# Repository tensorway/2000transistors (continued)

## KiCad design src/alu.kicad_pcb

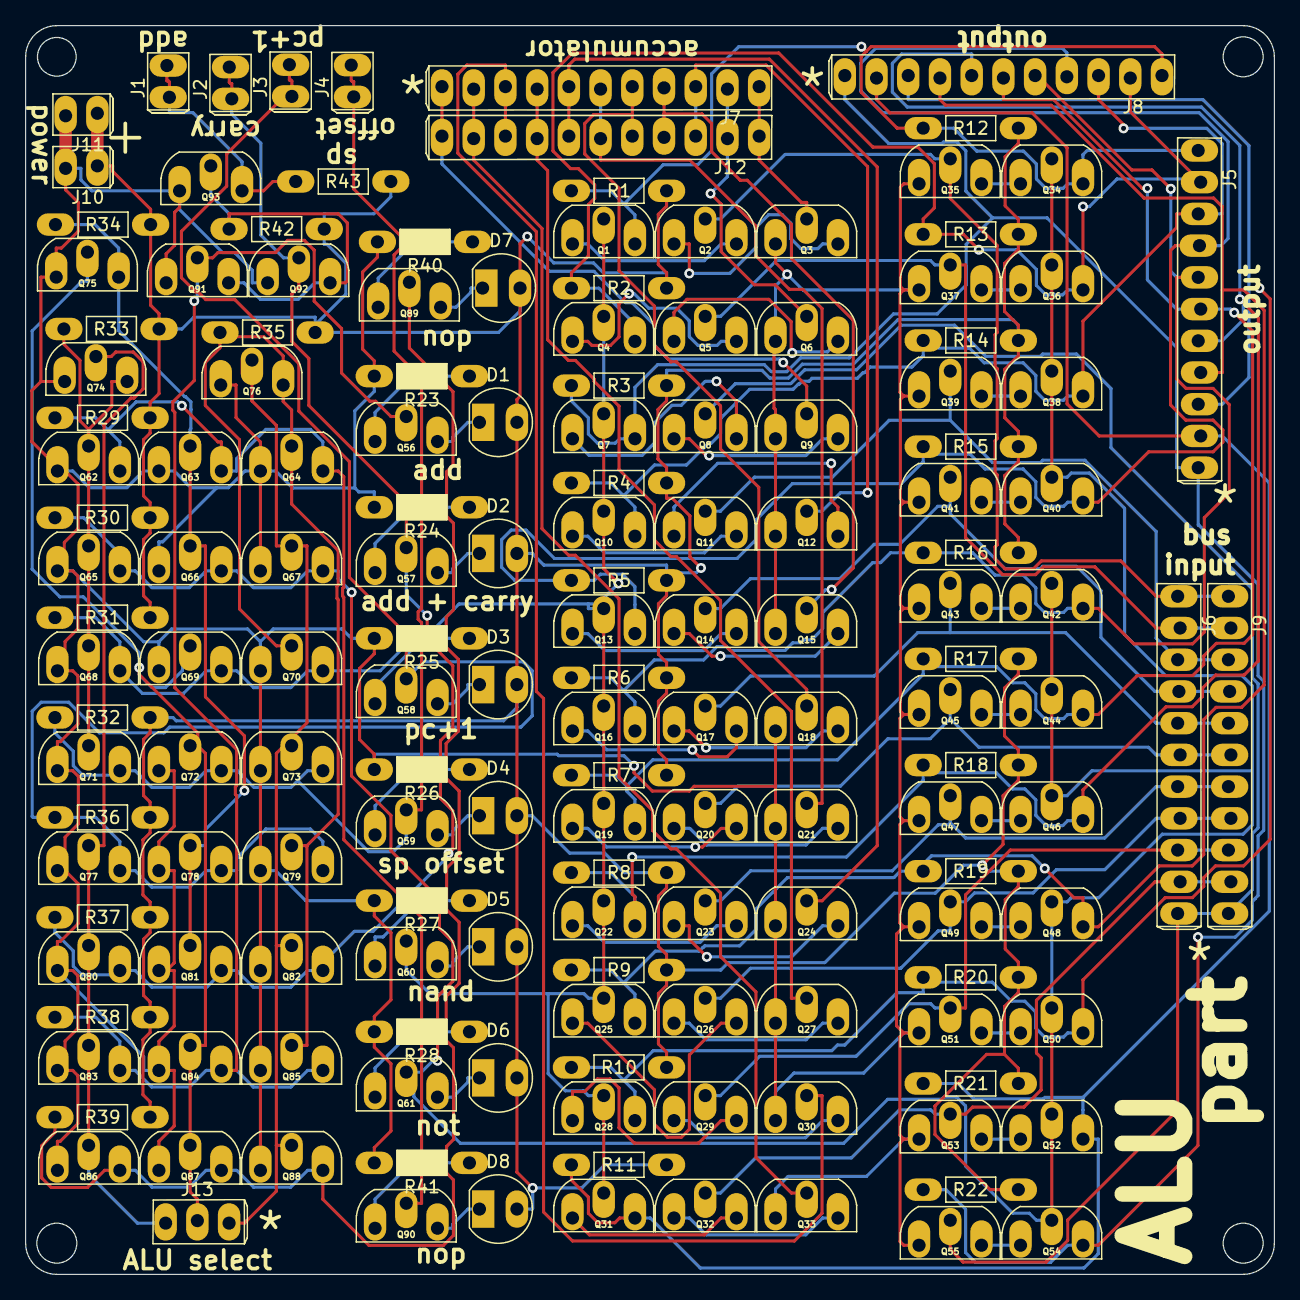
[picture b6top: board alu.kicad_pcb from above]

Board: 2 copper layers, 100.0 x 100.0 mm, 157 parts (0 on the bottom side), 100 nets.

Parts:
D1, D2, D3, D4, D5, D6, D7, D8: LED; led_5mm_tight
J1: add; 2pin_tight
J2: carry; 2pin_tight
J3: pc+1; 2pin_tight
J4: sp offset; 2pin_tight
J5, J6, J7, J8, J9, J12: Conn_01x11_Male; 11pin_tight
J10, J11: Conn_01x02_Male; 2pin_tight
J13: alu_sel; 3pin_tight
Q1, Q2, Q3, Q4, Q5, Q6, Q7, Q8, Q9, Q10, Q11, Q12, Q13, Q14, Q15, Q16, Q17, Q18, Q19, Q20, Q21, Q22, Q23, Q24, Q25, Q26, Q27, Q28, Q29, Q30, Q31, Q32, Q33, Q34, Q35, Q36, Q37, Q38, Q39, Q40, Q41, Q42, Q43, Q44, Q45, Q46, Q47, Q48, Q49, Q50, Q51, Q52, Q53, Q54, Q55, Q56, Q57, Q58, Q59, Q60, Q61, Q62, Q63, Q64, Q65, Q66, Q67, Q68, Q69, Q70, Q71, Q72, Q73, Q74, Q75, Q76, Q77, Q78, Q79, Q80, Q81, Q82, Q83, Q84, Q85, Q86, Q87, Q88, Q89, Q90, Q91, Q92, Q93: 2N7000; 2n7000_tight
R1, R2, R3, R4, R5, R6, R7, R8, R9, R10, R11, R12, R13, R14, R15, R16, R17, R18, R19, R20, R21, R22, R29, R30, R31, R32, R33, R34, R35, R36, R37, R38, R39, R42, R43: R; resistor_tight
R23, R24, R25, R26, R27, R28, R40, R41: R; resistor_led_tight

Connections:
+5V: D1.2, D2.2, D3.2, D4.2, D5.2, D6.2, D7.2, D8.2, J10.1, J11.1, R1.1, R2.1, R3.1, R4.1, R5.1, R6.1, R7.1, R8.1, R9.1, R10.1, R11.1, R12.1, R13.1, R14.1, R15.1, R16.1, R17.1, R18.1, R19.1, R20.1, R21.1, R22.1, R29.1, R30.1, R31.1, R32.1, R33.1, R34.1, R35.1, R36.1, R37.1, R38.1, R39.1, R42.1, R43.1
/Sheet63BFA3AE/Sheet63BAB2B1/a: Q62.2, Q65.2, Q68.2, Q71.2, Q74.3, R33.2
/Sheet63BFA3AE/Sheet63BAB2B1/b: Q63.2, Q66.2, Q75.3, Q78.2, Q81.2, R34.2
/Sheet63BFA3AE/Sheet63BAB2B1/c: Q64.2, Q70.2, Q76.3, Q79.2, Q85.2, R35.2
/Sheet63BFA3AE/a: Q86.3, Q87.3, Q88.3, Q89.2, R39.2
/Sheet63BFA3AE/ain: J13.1, Q74.2, Q77.2, Q80.2, Q83.2, Q86.2
/Sheet63BFA3AE/bin: J13.2, Q69.2, Q72.2, Q75.2, Q84.2, Q87.2
/Sheet63BFA3AE/cin: J13.3, Q67.2, Q73.2, Q76.2, Q82.2, Q88.2
/Sheet63BFA3AE/d: J3.1, J3.2, Q58.2, Q77.3, Q78.3, Q79.3, R36.2
/Sheet63BFA3AE/e: J4.1, J4.2, Q59.2, Q71.3, Q72.3, Q73.3, R32.2
/Sheet63BFA3AE/h: Q62.3, Q63.3, Q64.3, Q90.2, R29.2
/Sheet63BFDF12/a0: J6.1, J9.1, Q2.2, Q35.2
/Sheet63BFDF12/a1: J6.2, J9.2, Q5.2, Q37.2
/Sheet63BFDF12/a2: J6.3, J9.3, Q11.2, Q39.2
/Sheet63BFDF12/a3: J6.4, J9.4, Q14.2, Q41.2
/Sheet63BFDF12/a4: J6.5, J9.5, Q17.2, Q43.2
/Sheet63BFDF12/a5: J6.6, J9.6, Q20.2, Q45.2
/Sheet63BFDF12/a6: J6.7, J9.7, Q23.2, Q47.2
/Sheet63BFDF12/a7: J6.8, J9.8, Q26.2, Q49.2
/Sheet63BFDF12/a8: J6.9, J9.9, Q29.2, Q51.2
/Sheet63BFDF12/a9: J6.10, J9.10, Q32.2, Q53.2
/Sheet63BFDF12/a10: J6.11, J9.11, Q8.2, Q55.2
/Sheet63BFDF12/b0: J7.1, J12.1, Q3.2
/Sheet63BFDF12/b1: J7.2, J12.2, Q6.2
/Sheet63BFDF12/b2: J7.3, J12.3, Q12.2
/Sheet63BFDF12/b3: J7.4, J12.4, Q15.2
/Sheet63BFDF12/b4: J7.5, J12.5, Q18.2
/Sheet63BFDF12/b5: J7.6, J12.6, Q21.2
/Sheet63BFDF12/b6: J7.7, J12.7, Q24.2
/Sheet63BFDF12/b7: J7.8, J12.8, Q27.2
/Sheet63BFDF12/b8: J7.9, J12.9, Q30.2
/Sheet63BFDF12/b9: J7.10, J12.10, Q33.2
/Sheet63BFDF12/b10: J7.11, J12.11, Q9.2
/Sheet63BFDF12/enable: Q1.2, Q4.2, Q7.2, Q10.2, Q13.2, Q16.2, Q19.2, Q22.2, Q25.2, Q28.2, Q31.2, Q60.2, Q68.3, Q69.3, Q70.3, R31.2
/Sheet63BFDF12/out0: J5.1, J8.1, Q1.3, Q34.3, R1.2, R12.2
/Sheet63BFDF12/out1: J5.2, J8.2, Q4.3, Q36.3, R2.2, R13.2
/Sheet63BFDF12/out2: J5.3, J8.3, Q10.3, Q38.3, R4.2, R14.2
/Sheet63BFDF12/out3: J5.4, J8.4, Q13.3, Q40.3, R5.2, R15.2
/Sheet63BFDF12/out4: J5.5, J8.5, Q16.3, Q42.3, R6.2, R16.2
/Sheet63BFDF12/out5: J5.6, J8.6, Q19.3, Q44.3, R7.2, R17.2
/Sheet63BFDF12/out6: J5.7, J8.7, Q22.3, Q46.3, R8.2, R18.2
/Sheet63BFDF12/out7: J5.8, J8.8, Q25.3, Q48.3, R9.2, R19.2
/Sheet63BFDF12/out8: J5.9, J8.9, Q28.3, Q50.3, R10.2, R20.2
/Sheet63BFDF12/out9: J5.10, J8.10, Q31.3, Q52.3, R11.2, R21.2
/Sheet63BFDF12/out10: J5.11, J8.11, Q7.3, Q54.3, R3.2, R22.2
/Sheet648070F7/a: Q56.2, Q83.3, Q84.3, Q85.3, Q91.2, R38.2
/Sheet648070F7/b: J2.1, J2.2, Q57.2, Q80.3, Q81.3, Q82.3, Q92.2, R37.2
/Sheet64807415/in: Q91.3, Q92.3, Q93.2, R42.2
/Sheet64807415/out: J1.1, J1.2, Q93.3, R43.2
/sheet63E1DFB6/enable: Q34.2, Q36.2, Q38.2, Q40.2, Q42.2, Q44.2, Q46.2, Q48.2, Q50.2, Q52.2, Q54.2, Q61.2, Q65.3, Q66.3, Q67.3, R30.2
GND: J10.2, J11.2, Q3.1, Q6.1, Q9.1, Q12.1, Q15.1, Q18.1, Q21.1, Q24.1, Q27.1, Q30.1, Q33.1, Q35.1, Q37.1, Q39.1, Q41.1, Q43.1, Q45.1, Q47.1, Q49.1, Q51.1, Q53.1, Q55.1, Q62.1, Q63.1, Q64.1, Q65.1, Q66.1, Q67.1, Q68.1, Q69.1, Q70.1, Q71.1, Q72.1, Q73.1, Q74.1, Q75.1, Q76.1, Q77.1, Q78.1, Q79.1, Q80.1, Q81.1, Q82.1, Q83.1, Q84.1, Q85.1, Q86.1, Q87.1, Q88.1, Q91.1, Q92.1, Q93.1, R23.2, R24.2, R25.2, R26.2, R27.2, R28.2, R40.2, R41.2
unnamed: D1.1, Q56.3
unnamed: D2.1, Q57.3
unnamed: D3.1, Q58.3
unnamed: D4.1, Q59.3
unnamed: D5.1, Q60.3
unnamed: D6.1, Q61.3
unnamed: D7.1, Q89.3
unnamed: D8.1, Q90.3
unnamed: Q1.1, Q2.3
unnamed: Q2.1, Q3.3
unnamed: Q4.1, Q5.3
unnamed: Q5.1, Q6.3
unnamed: Q7.1, Q8.3
unnamed: Q8.1, Q9.3
unnamed: Q10.1, Q11.3
unnamed: Q11.1, Q12.3
unnamed: Q13.1, Q14.3
unnamed: Q14.1, Q15.3
unnamed: Q16.1, Q17.3
unnamed: Q17.1, Q18.3
unnamed: Q19.1, Q20.3
unnamed: Q20.1, Q21.3
unnamed: Q22.1, Q23.3
unnamed: Q23.1, Q24.3
unnamed: Q25.1, Q26.3
unnamed: Q26.1, Q27.3
unnamed: Q28.1, Q29.3
unnamed: Q29.1, Q30.3
unnamed: Q31.1, Q32.3
unnamed: Q32.1, Q33.3
unnamed: Q34.1, Q35.3
unnamed: Q36.1, Q37.3
unnamed: Q38.1, Q39.3
unnamed: Q40.1, Q41.3
unnamed: Q42.1, Q43.3
unnamed: Q44.1, Q45.3
unnamed: Q46.1, Q47.3
unnamed: Q48.1, Q49.3
unnamed: Q50.1, Q51.3
unnamed: Q52.1, Q53.3
unnamed: Q54.1, Q55.3
unnamed: Q56.1, R23.1
unnamed: Q57.1, R24.1
unnamed: Q58.1, R25.1
unnamed: Q59.1, R26.1
unnamed: Q60.1, R27.1
unnamed: Q61.1, R28.1
unnamed: Q89.1, R40.1
unnamed: Q90.1, R41.1

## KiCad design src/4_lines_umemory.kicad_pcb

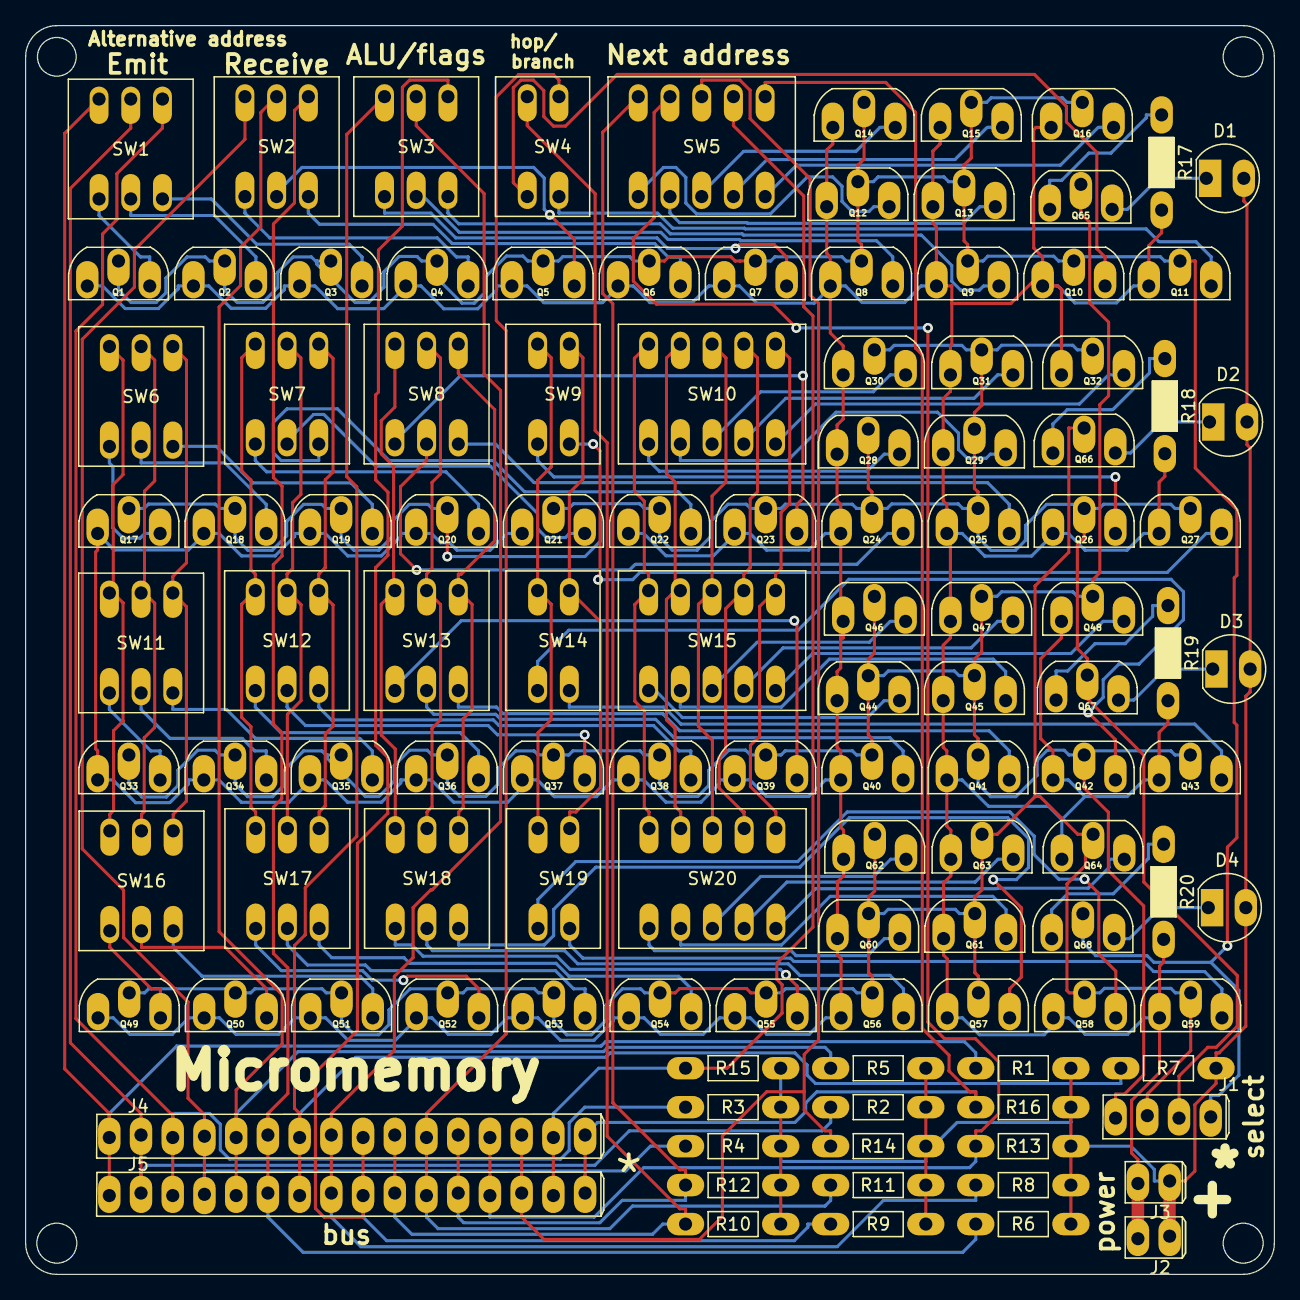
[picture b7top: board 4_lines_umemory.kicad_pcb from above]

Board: 2 copper layers, 100.0 x 100.0 mm, 117 parts (0 on the bottom side), 110 nets.

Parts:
D1, D2, D3, D4: LED; led_5mm_tight
J1: Conn_01x04_Male; 4pin_tight
J2, J3: Conn_01x02_Male; 2pin_tight
J4, J5: Conn_01x16_Male; 16pin_tight
Q1, Q2, Q3, Q4, Q5, Q6, Q7, Q8, Q9, Q10, Q11, Q12, Q13, Q14, Q15, Q16, Q17, Q18, Q19, Q20, Q21, Q22, Q23, Q24, Q25, Q26, Q27, Q28, Q29, Q30, Q31, Q32, Q33, Q34, Q35, Q36, Q37, Q38, Q39, Q40, Q41, Q42, Q43, Q44, Q45, Q46, Q47, Q48, Q49, Q50, Q51, Q52, Q53, Q54, Q55, Q56, Q57, Q58, Q59, Q60, Q61, Q62, Q63, Q64, Q65, Q66, Q67, Q68: 2N7000; 2n7000_tight
R1, R2, R3, R4, R5, R6, R7, R8, R9, R10, R11, R12, R13, R14, R15, R16: R; resistor_tight
R17, R18, R19, R20: R; resistor_led_tight
SW1, SW2, SW3, SW6, SW7, SW8, SW11, SW12, SW13, SW16, SW17, SW18: SW_DIP_x03; dip3_switch
SW4, SW9, SW14, SW19: SW_DIP_x02; dip2_switch
SW5, SW10, SW15, SW20: SW_DIP_x05; dip5_switch

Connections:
+5V: D1.2, D2.2, D3.2, D4.2, J2.1, J3.1, R1.1, R2.1, R3.1, R4.1, R5.1, R6.1, R7.1, R8.1, R9.1, R10.1, R11.1, R12.1, R13.1, R14.1, R15.1, R16.1
/Sheet63D9F596/a: J4.1, J5.1, R1.2, SW1.3
/Sheet63D9F596/b: J4.2, J5.2, R2.2, SW1.2
/Sheet63D9F596/c: J4.3, J5.3, R3.2, SW1.1
/Sheet63D9F596/d: J4.4, J5.4, R4.2, SW2.3
/Sheet63D9F596/e: J4.5, J5.5, R5.2, SW2.2
/Sheet63D9F596/enable: J1.4, Q1.2, Q2.2, Q3.2, Q4.2, Q5.2, Q6.2, Q7.2, Q8.2, Q9.2, Q10.2, Q11.2, Q12.2, Q13.2, Q14.2, Q15.2, Q16.2, Q68.2
/Sheet63D9F596/f: J4.6, J5.6, R6.2, SW2.1
/Sheet63D9F596/g: J4.7, J5.7, R7.2, SW3.3
/Sheet63D9F596/h: J4.8, J5.8, R8.2, SW3.2
/Sheet63D9F596/i: J4.9, J5.9, R9.2, SW3.1
/Sheet63D9F596/j: J4.10, J5.10, R10.2, SW4.2
/Sheet63D9F596/k: J4.11, J5.11, R11.2, SW4.1
/Sheet63D9F596/l: J4.12, J5.12, R12.2, SW5.5
/Sheet63D9F596/m: J4.13, J5.13, R13.2, SW5.4
/Sheet63D9F596/n: J4.14, J5.14, R14.2, SW5.3
/Sheet63D9F596/o: J4.15, J5.15, R15.2, SW5.2
/Sheet63D9F596/p: J4.16, J5.16, R16.2, SW5.1
/sheet63DAA910/a: SW6.3, SW11.3, SW16.3
/sheet63DAA910/b: SW6.2, SW11.2, SW16.2
/sheet63DAA910/c: SW6.1, SW11.1, SW16.1
/sheet63DAA910/d: SW7.3, SW12.3, SW17.3
/sheet63DAA910/e: SW7.2, SW12.2, SW17.2
/sheet63DAA910/enable: J1.3, Q17.2, Q18.2, Q19.2, Q20.2, Q21.2, Q22.2, Q23.2, Q24.2, Q25.2, Q26.2, Q27.2, Q28.2, Q29.2, Q30.2, Q31.2, Q32.2, Q67.2
/sheet63DAA910/f: SW7.1, SW12.1, SW17.1
/sheet63DAA910/g: SW8.3, SW13.3, SW18.3
/sheet63DAA910/h: SW8.2, SW13.2, SW18.2
/sheet63DAA910/i: SW8.1, SW13.1, SW18.1
/sheet63DAA910/j: SW9.2, SW14.2, SW19.2
/sheet63DAA910/k: SW9.1, SW14.1, SW19.1
/sheet63DAA910/l: SW10.5, SW15.5, SW20.5
/sheet63DAA910/m: SW10.4, SW15.4, SW20.4
/sheet63DAA910/n: SW10.3, SW15.3, SW20.3
/sheet63DAA910/o: SW10.2, SW15.2, SW20.2
/sheet63DAA910/p: SW10.1, SW15.1, SW20.1
/sheet63DB6C5D/enable: J1.2, Q49.2, Q50.2, Q51.2, Q52.2, Q53.2, Q54.2, Q55.2, Q56.2, Q57.2, Q58.2, Q59.2, Q60.2, Q61.2, Q62.2, Q63.2, Q64.2, Q66.2
/sheet63DBEA91/enable: J1.1, Q33.2, Q34.2, Q35.2, Q36.2, Q37.2, Q38.2, Q39.2, Q40.2, Q41.2, Q42.2, Q43.2, Q44.2, Q45.2, Q46.2, Q47.2, Q48.2, Q65.2
GND: J2.2, J3.2, Q1.1, Q2.1, Q3.1, Q4.1, Q5.1, Q6.1, Q7.1, Q8.1, Q9.1, Q10.1, Q11.1, Q12.1, Q13.1, Q14.1, Q15.1, Q16.1, Q17.1, Q18.1, Q19.1, Q20.1, Q21.1, Q22.1, Q23.1, Q24.1, Q25.1, Q26.1, Q27.1, Q28.1, Q29.1, Q30.1, Q31.1, Q32.1, Q33.1, Q34.1, Q35.1, Q36.1, Q37.1, Q38.1, Q39.1, Q40.1, Q41.1, Q42.1, Q43.1, Q44.1, Q45.1, Q46.1, Q47.1, Q48.1, Q49.1, Q50.1, Q51.1, Q52.1, Q53.1, Q54.1, Q55.1, Q56.1, Q57.1, Q58.1, Q59.1, Q60.1, Q61.1, Q62.1, Q63.1, Q64.1, R17.2, R18.2, R19.2, R20.2
unnamed: D1.1, Q65.3
unnamed: D2.1, Q66.3
unnamed: D3.1, Q67.3
unnamed: D4.1, Q68.3
unnamed: Q1.3, SW1.4
unnamed: Q2.3, SW1.5
unnamed: Q3.3, SW1.6
unnamed: Q4.3, SW2.4
unnamed: Q5.3, SW2.5
unnamed: Q6.3, SW2.6
unnamed: Q7.3, SW3.4
unnamed: Q8.3, SW3.5
unnamed: Q9.3, SW3.6
unnamed: Q10.3, SW4.3
unnamed: Q11.3, SW4.4
unnamed: Q12.3, SW5.6
unnamed: Q13.3, SW5.7
unnamed: Q14.3, SW5.8
unnamed: Q15.3, SW5.9
unnamed: Q16.3, SW5.10
unnamed: Q17.3, SW6.4
unnamed: Q18.3, SW6.5
unnamed: Q19.3, SW6.6
unnamed: Q20.3, SW7.4
unnamed: Q21.3, SW7.5
unnamed: Q22.3, SW7.6
unnamed: Q23.3, SW8.4
unnamed: Q24.3, SW8.5
unnamed: Q25.3, SW8.6
unnamed: Q26.3, SW9.3
unnamed: Q27.3, SW9.4
unnamed: Q28.3, SW10.6
unnamed: Q29.3, SW10.7
unnamed: Q30.3, SW10.8
unnamed: Q31.3, SW10.9
unnamed: Q32.3, SW10.10
unnamed: Q33.3, SW11.4
unnamed: Q34.3, SW11.5
unnamed: Q35.3, SW11.6
unnamed: Q36.3, SW12.4
unnamed: Q37.3, SW12.5
unnamed: Q38.3, SW12.6
unnamed: Q39.3, SW13.4
unnamed: Q40.3, SW13.5
unnamed: Q41.3, SW13.6
unnamed: Q42.3, SW14.3
unnamed: Q43.3, SW14.4
unnamed: Q44.3, SW15.6
unnamed: Q45.3, SW15.7
unnamed: Q46.3, SW15.8
unnamed: Q47.3, SW15.9
unnamed: Q48.3, SW15.10
unnamed: Q49.3, SW16.4
unnamed: Q50.3, SW16.5
unnamed: Q51.3, SW16.6
unnamed: Q52.3, SW17.4
unnamed: Q53.3, SW17.5
unnamed: Q54.3, SW17.6
unnamed: Q55.3, SW18.4
unnamed: Q56.3, SW18.5
unnamed: Q57.3, SW18.6
unnamed: Q58.3, SW19.3
unnamed: Q59.3, SW19.4
unnamed: Q60.3, SW20.6
unnamed: Q61.3, SW20.7
unnamed: Q62.3, SW20.8
unnamed: Q63.3, SW20.9
unnamed: Q64.3, SW20.10
unnamed: Q65.1, R17.1
unnamed: Q66.1, R18.1
unnamed: Q67.1, R19.1
unnamed: Q68.1, R20.1

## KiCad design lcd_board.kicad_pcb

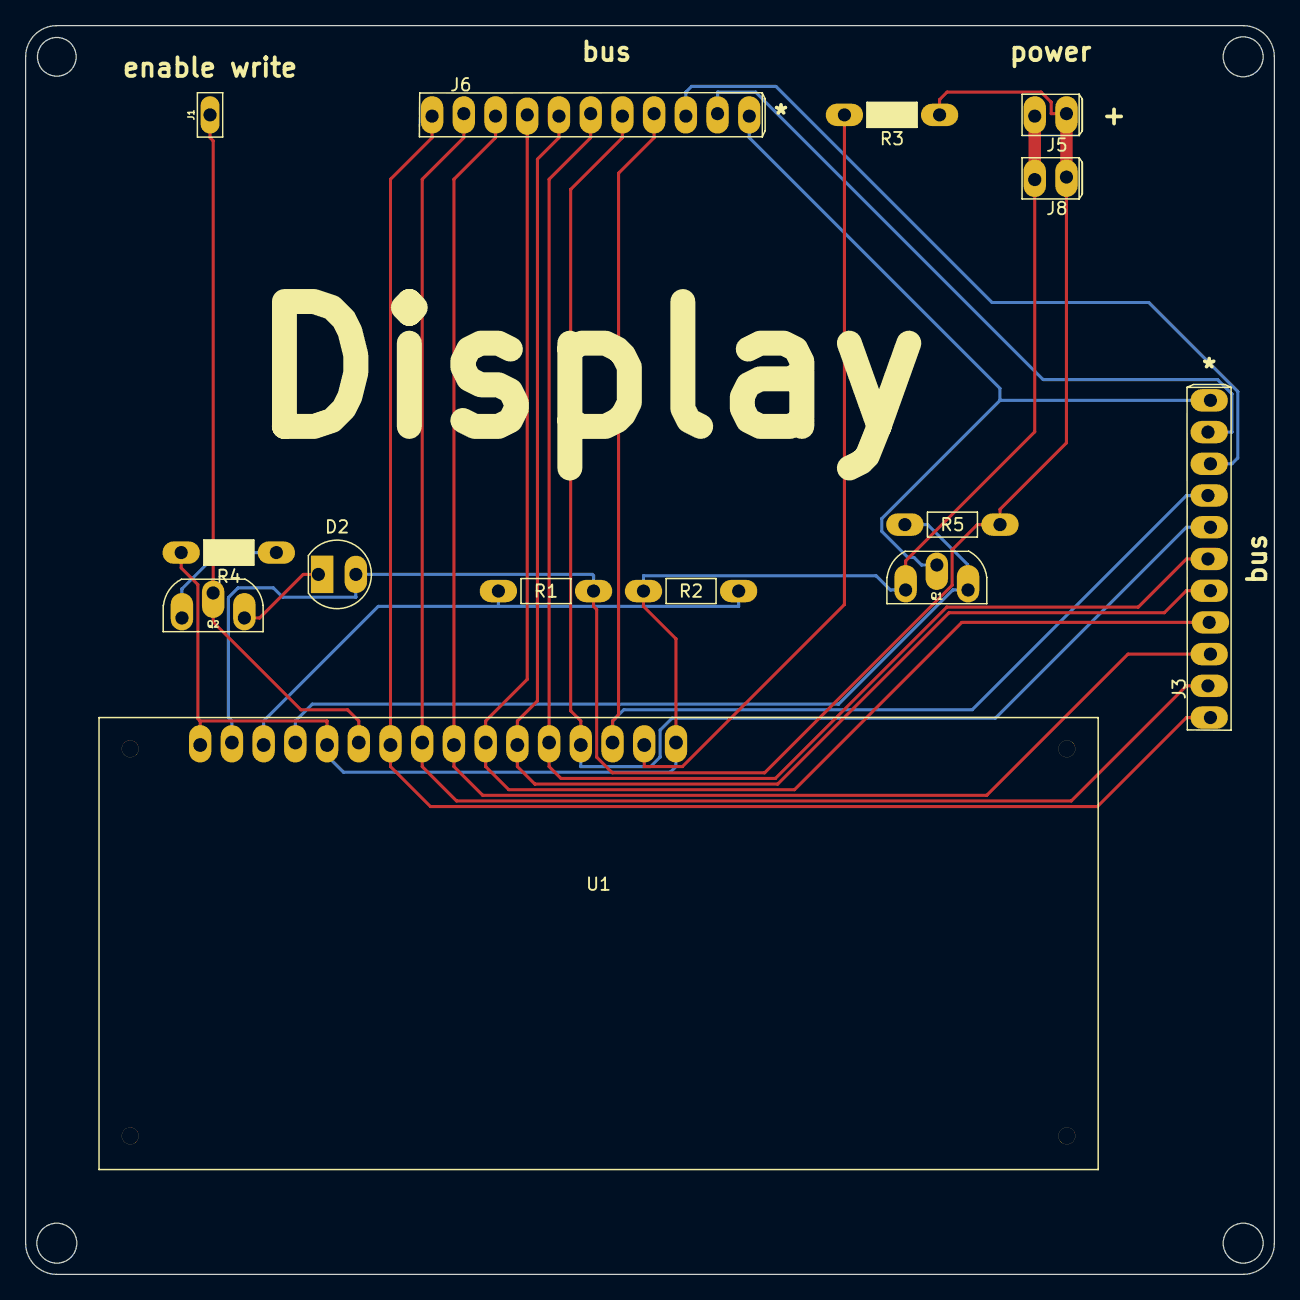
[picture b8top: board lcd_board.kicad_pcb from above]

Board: 2 copper layers, 100.0 x 100.0 mm, 14 parts (0 on the bottom side), 19 nets.

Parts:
D2: LED; led_5mm_tight
J1: Conn_01x01_Male; 1pin
J3, J6: Conn_01x11_Male; 11pin_tight
J5, J8: Conn_01x02_Male; 2pin_tight
Q1, Q2: 2N7000; 2n7000_tight
R1, R2, R5: R; resistor_tight
R3, R4: R; resistor_led_tight
U1: lcd_display

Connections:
+5V: D2.2, J5.1, J8.1, R1.1, R3.1, R5.1, U1.5v
/Sheet63DF1E83/in: J3.11, J6.11, Q1.2
/Sheet63DF1E83/out: Q1.3, R5.2, U1.register_select
/sheet63DE894A/in: J1.1, Q2.2, U1.enable
GND: J5.2, J8.2, Q1.1, R2.2, R4.2, U1.gnd, U1.led_negative, U1.read/write
unnamed: D2.1, Q2.3
unnamed: J3.1, J6.1, U1.d0
unnamed: J3.2, J6.2, U1.d1
unnamed: J3.3, J6.3, U1.d2
unnamed: J3.4, J6.4, U1.d3
unnamed: J3.5, J6.5, U1.d4
unnamed: J3.6, J6.6, U1.d5
unnamed: J3.7, J6.7, U1.d6
unnamed: J3.8, J6.8, U1.d7
unnamed: J3.9, J6.9
unnamed: J3.10, J6.10
unnamed: Q2.1, R4.1
unnamed: R1.2, R2.1, U1.contrast
unnamed: R3.2, U1.led_positive

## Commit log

2023-10-25 added readme
2023-10-25 reorg to folder
2023-10-25 added components
